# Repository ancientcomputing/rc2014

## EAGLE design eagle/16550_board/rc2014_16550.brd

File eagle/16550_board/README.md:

The board has been tested and a BIOS and associated Monitor/Debugger/BASIC binaries released.
<p>
The board is also available from OSH Park at the following link:
<p>
<a href="https://www.oshpark.com/shared_projects/1SkkN4ey"></img></a>
<p>
Note that I do not have any relationship with OSH Park other than that of a customer.
<p>
Copyright Ben Chong and licensed freely back to the community.

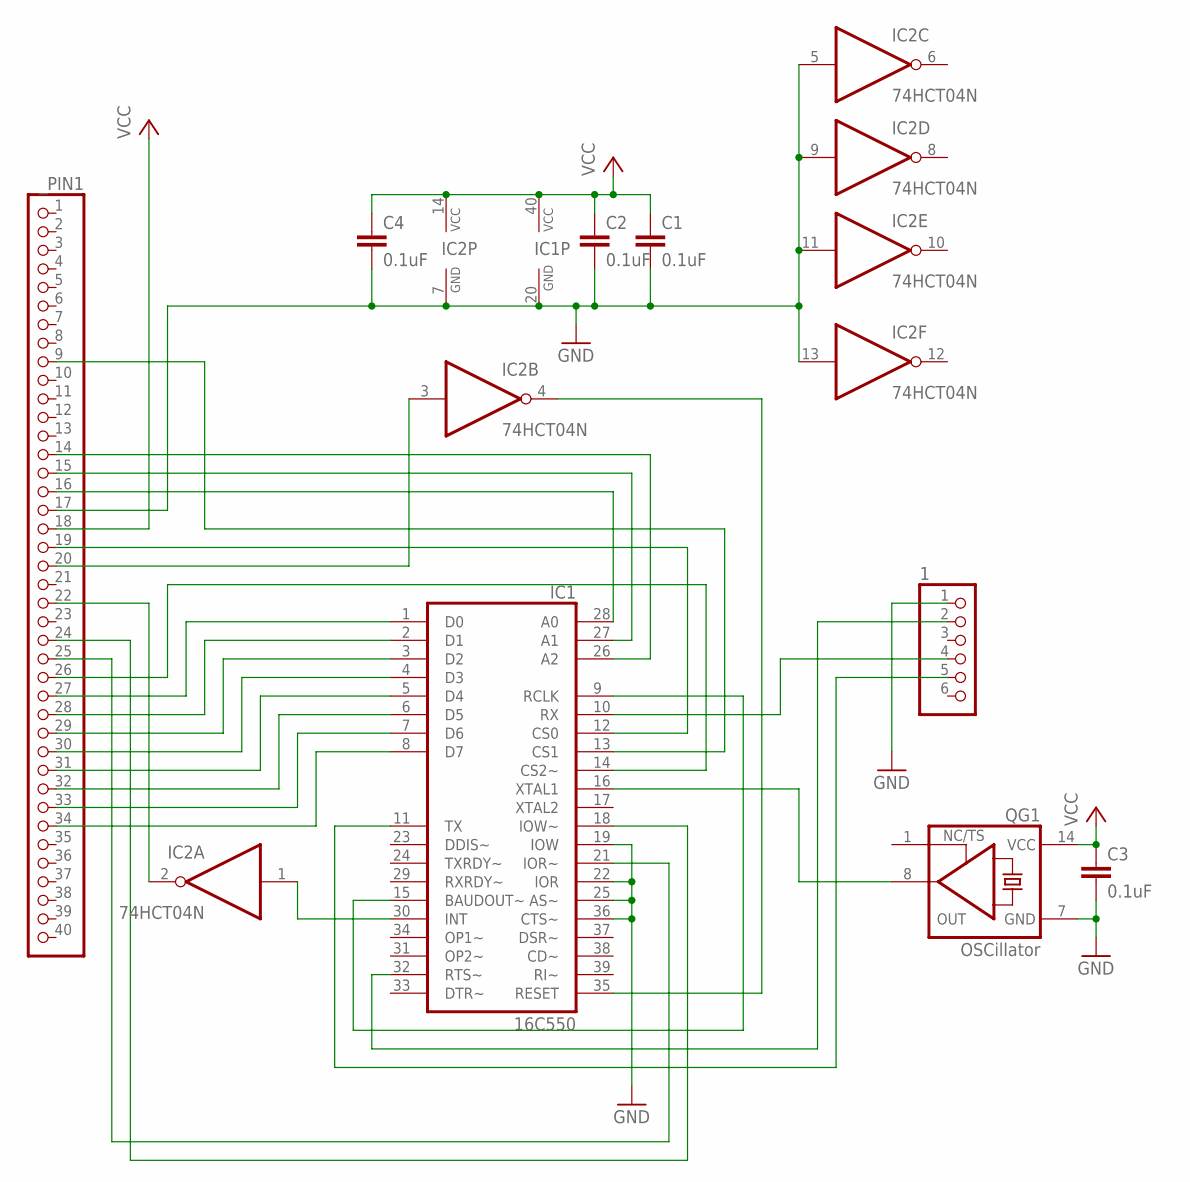
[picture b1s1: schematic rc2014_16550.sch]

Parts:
1: PINHD-1X6; 1X06
C1, C2, C3, C4: 0.1uF; C050-024X044
IC1: 16C550; DIL40
IC2: 74HCT04N; DIL14
QG1: OSCillator; DIL14S
_PIN1: PINHD-1X40; 1X40

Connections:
/INT: IC2.2 (O), _PIN1.22
/IORQ: IC1.14 (CS2~), _PIN1.26
/M1: IC1.12 (CS0), _PIN1.19
/RD: IC1.21 (IOR~), _PIN1.25
/RST: IC2.3 (I), _PIN1.20
/RTS: 1.2, IC1.32 (RTS~)
/WR: IC1.18 (IOW~), _PIN1.24
A0: IC1.28 (A0), _PIN1.16
A1: IC1.27 (A1), _PIN1.15
A2: IC1.26 (A2), _PIN1.14
A7: IC1.13 (CS1), _PIN1.9
D0: IC1.1 (D0), _PIN1.27
D1: IC1.2 (D1), _PIN1.28
D2: IC1.3 (D2), _PIN1.29
D3: IC1.4 (D3), _PIN1.30
D4: IC1.5 (D4), _PIN1.31
D5: IC1.6 (D5), _PIN1.32
D6: IC1.7 (D6), _PIN1.33
D7: IC1.8 (D7), _PIN1.34
GND: 1.1, C1.2, C2.2, C3.2, C4.2, IC1.19 (IOW), IC1.20 (GND), IC1.22 (IOR), IC1.25 (AS~), IC1.36 (CTS~), IC2.5 (I), IC2.7 (GND), IC2.9 (I), IC2.11 (I), IC2.13 (I), QG1.7 (GND), _PIN1.17
INT: IC1.30 (INT), IC2.1 (I)
unnamed: IC1.9 (RCLK), IC1.15 (BAUDOUT~)
OSC: IC1.16 (XTAL1), QG1.8 (OUT)
RESET: IC1.35 (RESET), IC2.4 (O)
RX: 1.4, IC1.10 (RX)
TX: 1.5, IC1.11 (TX)
VCC: C1.1, C2.1, C3.1, C4.1, IC1.40 (VCC), IC2.14 (VCC), QG1.14 (VCC), _PIN1.18

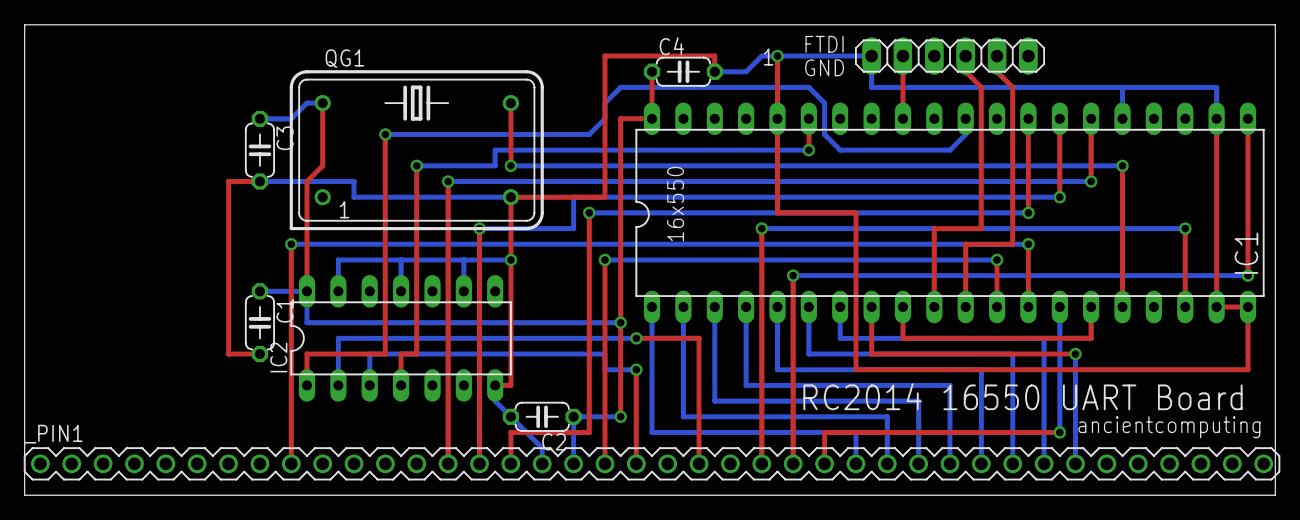
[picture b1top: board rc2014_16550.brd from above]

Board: 2 copper layers, 101.3 x 38.1 mm, 9 parts (0 on the bottom side), 27 nets.

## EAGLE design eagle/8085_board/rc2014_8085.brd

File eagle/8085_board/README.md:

<b>8085 Processor Board for the RC2014</b>
<p>
Exposes SID/SOD to an FTDI header for UART-less serial.
<p>
Tested. Wiring error between reset RC network and pin 13 of he 74xx14. Fixed in this version.
<p>
<a href="https://www.oshpark.com/shared_projects/jnleN9Nv"></img></a>
<p>
A simple Monitor can be found in the <a href="https://github.com/ancientcomputing/rc2014/tree/master/rom/8085">rom/8085 folder</a>.
<p>
Copyright Ben Chong and licensed freely back to the community.

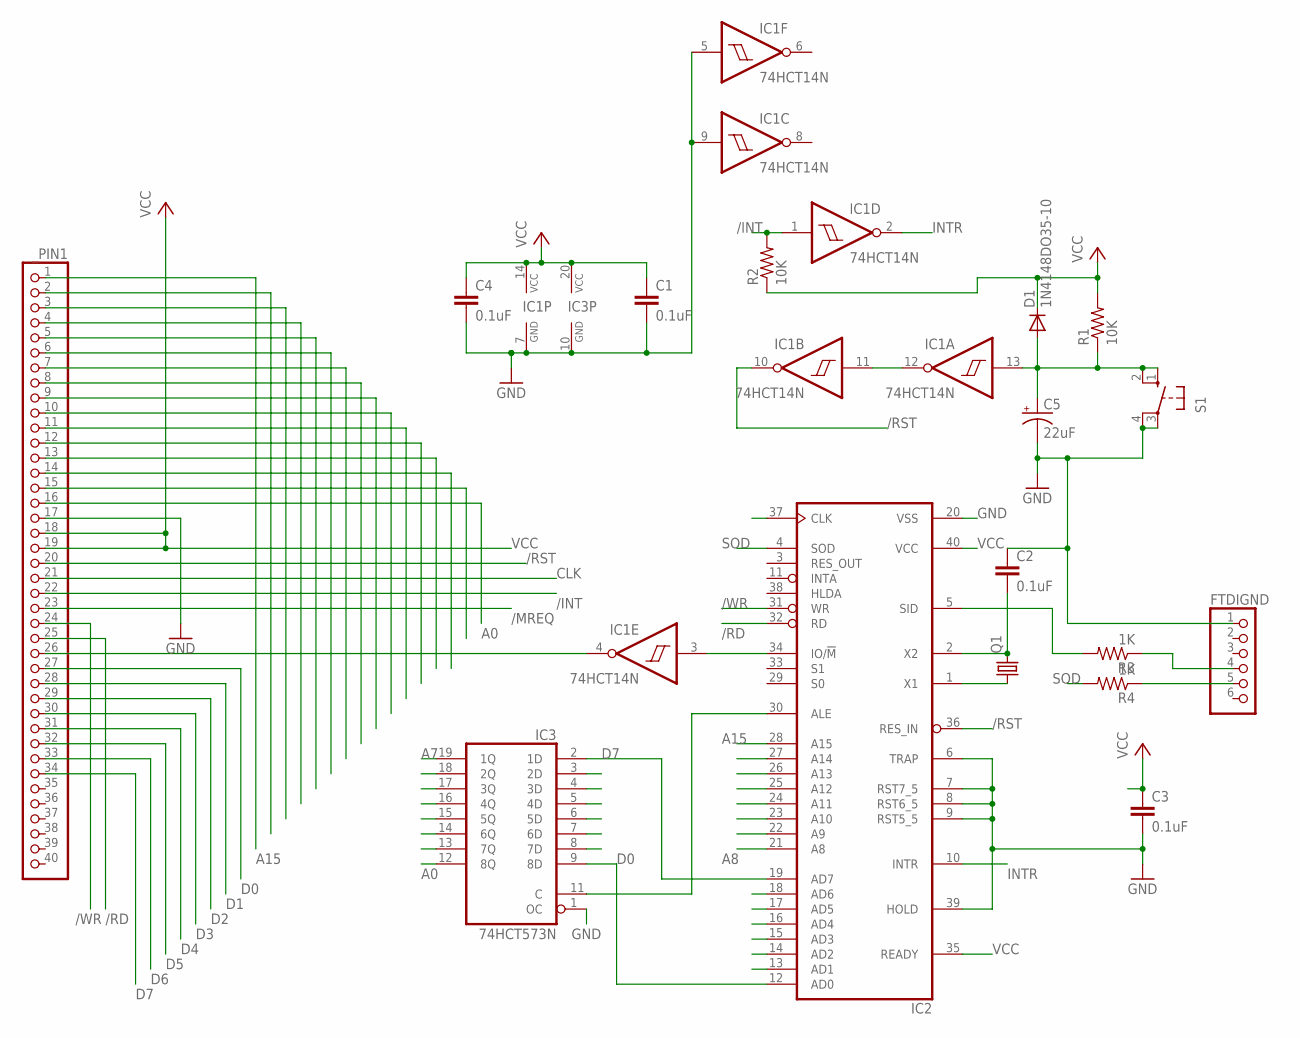
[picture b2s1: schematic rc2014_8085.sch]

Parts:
C1, C2, C3, C4: 0.1uF; C050-024X044
C5: 22uF; TAP5-80
D1: 1N4148DO35-10; DO35-10
FTDIGND: PINHD-1X6; 1X06
IC1: 74HCT14N; DIL14
IC2: 8085; DIL40
IC3: 74HCT573N; DIL20
Q1: CRYSTALHC49S; HC49/S
R1, R2: 10K; 0207/10
R3, R4: 1K; 0207/10
S1: 10-XX; B3F-10XX
_PIN1: PINHD-1X40; 1X40

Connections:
/INT: IC1.1 (I), R2.2, _PIN1.22
/IORQ: IC1.4 (O), _PIN1.26
/MREQ: IC1.3 (I), IC2.34 (IO/!M), _PIN1.23
/RD: IC2.32 (RD), _PIN1.25
/RST: IC1.10 (O), IC2.36 (RES_IN), _PIN1.20
/WR: IC2.31 (WR), _PIN1.24
A0: IC3.12 (8Q), _PIN1.16
A1: IC3.13 (7Q), _PIN1.15
A2: IC3.14 (6Q), _PIN1.14
A3: IC3.15 (5Q), _PIN1.13
A4: IC3.16 (4Q), _PIN1.12
A5: IC3.17 (3Q), _PIN1.11
A6: IC3.18 (2Q), _PIN1.10
A7: IC3.19 (1Q), _PIN1.9
A8: IC2.21 (A8), _PIN1.8
A9: IC2.22 (A9), _PIN1.7
A10: IC2.23 (A10), _PIN1.6
A11: IC2.24 (A11), _PIN1.5
A12: IC2.25 (A12), _PIN1.4
A13: IC2.26 (A13), _PIN1.3
A14: IC2.27 (A14), _PIN1.2
A15: IC2.28 (A15), _PIN1.1
ALE: IC2.30 (ALE), IC3.11 (C)
CLK: IC2.37 (CLK), _PIN1.21
D0: IC2.12 (AD0), IC3.9 (8D), _PIN1.27
D1: IC2.13 (AD1), IC3.8 (7D), _PIN1.28
D2: IC2.14 (AD2), IC3.7 (6D), _PIN1.29
D3: IC2.15 (AD3), IC3.6 (5D), _PIN1.30
D4: IC2.16 (AD4), IC3.5 (4D), _PIN1.31
D5: IC2.17 (AD5), IC3.4 (3D), _PIN1.32
D6: IC2.18 (AD6), IC3.3 (2D), _PIN1.33
D7: IC2.19 (AD7), IC3.2 (1D), _PIN1.34
GND: C1.2, C2.1, C3.2, C4.2, C5.-, FTDIGND.1, IC1.5 (I), IC1.7 (GND), IC1.9 (I), IC2.6 (TRAP), IC2.7 (RST7_5), IC2.8 (RST6_5), IC2.9 (RST5_5), IC2.20 (VSS), IC2.39 (HOLD), IC3.1 (OC), IC3.10 (GND), S1.3, S1.4 (P1), _PIN1.17
INTR: IC1.2 (O), IC2.10 (INTR)
unnamed: IC2.1 (X1), Q1.1
unnamed: C2.2, IC2.2 (X2), Q1.2
unnamed: IC1.11 (I), IC1.12 (O)
RESET: C5.+, D1.A, IC1.13 (I), R1.1, S1.1 (S), S1.2 (S1)
RX: FTDIGND.4, R3.1
SID: IC2.5 (SID), R3.2
SOD: IC2.4 (SOD), R4.2
TX: FTDIGND.5, R4.1
VCC: C1.1, C3.1, C4.1, D1.C, IC1.14 (VCC), IC2.35 (READY), IC2.40 (VCC), IC3.20 (VCC), R1.2, R2.1, _PIN1.18, _PIN1.19

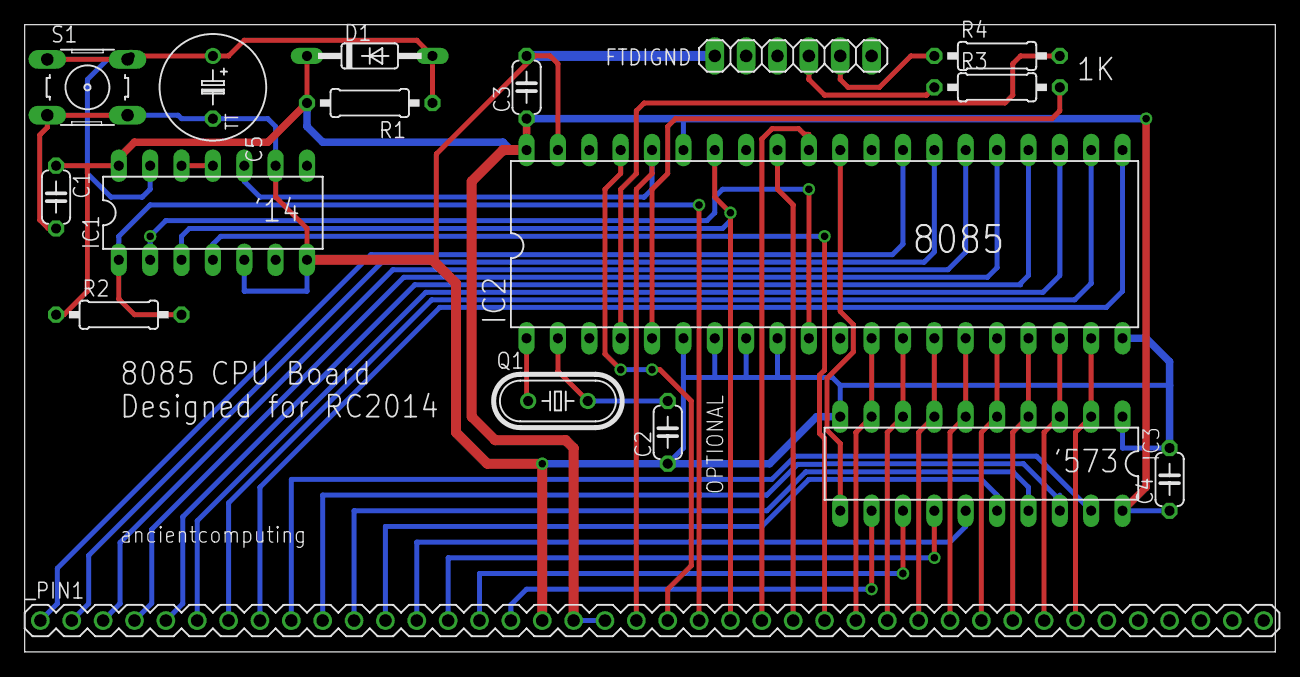
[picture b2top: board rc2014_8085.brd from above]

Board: 2 copper layers, 101.3 x 50.8 mm, 17 parts (0 on the bottom side), 43 nets.

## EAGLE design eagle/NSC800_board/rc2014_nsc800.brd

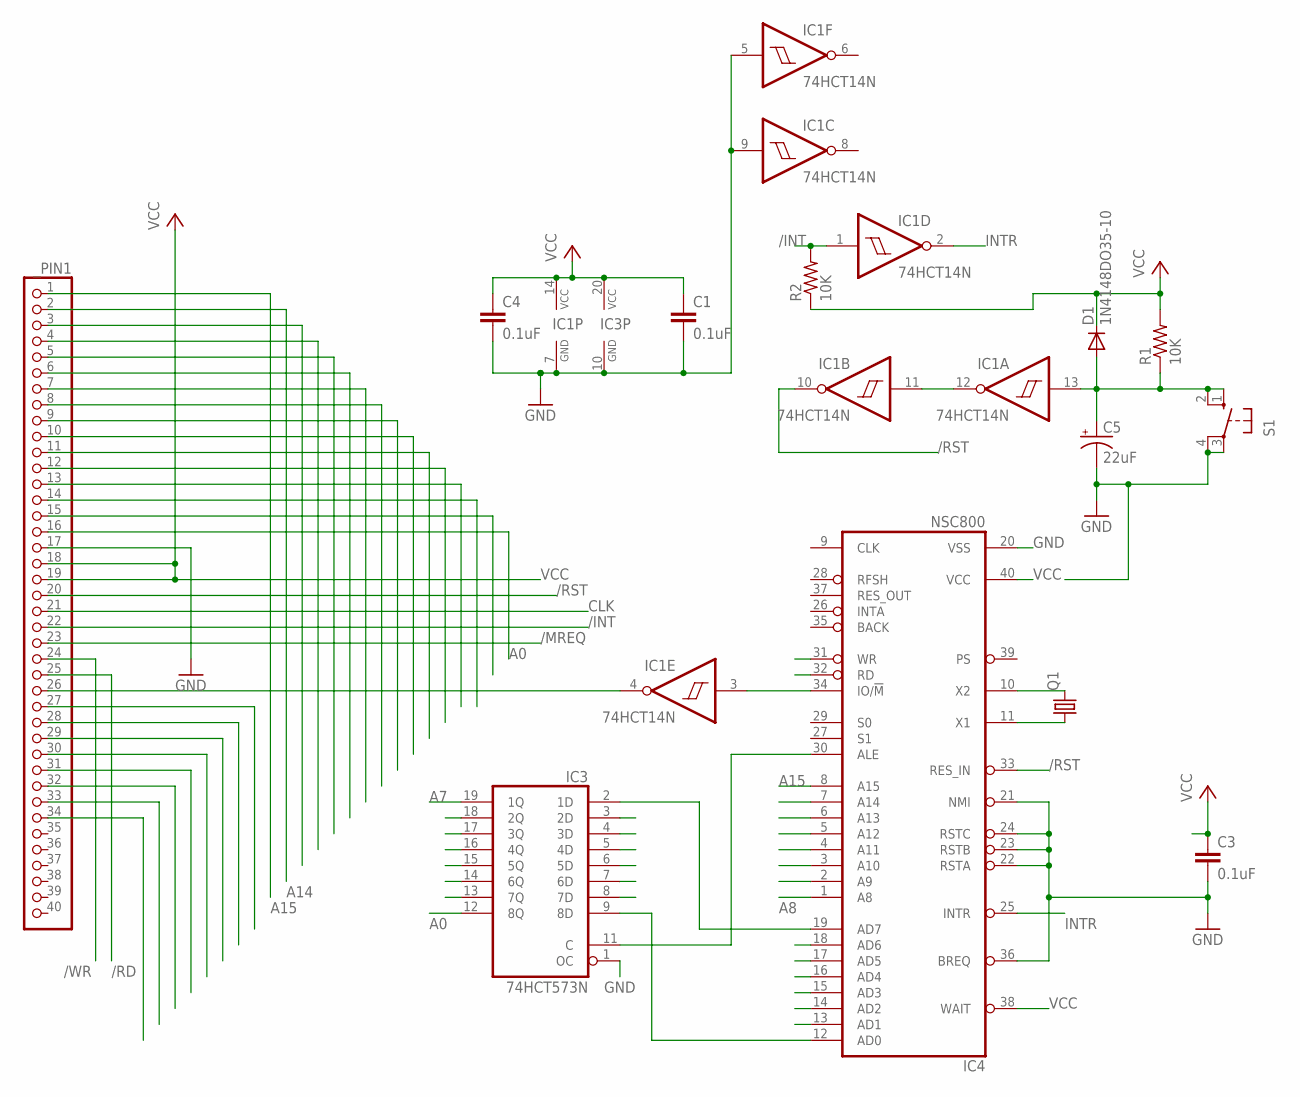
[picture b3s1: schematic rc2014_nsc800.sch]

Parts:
C1, C3, C4: 0.1uF; C050-024X044
C5: 22uF; TAP5-80
D1: 1N4148DO35-10; DO35-10
IC1: 74HCT14N; DIL14
IC3: 74HCT573N; DIL20
IC4: NSC800; DIL40
Q1: CRYSTALHC49S; HC49/S
R1, R2: 10K; 0207/10
S1: 10-XX; B3F-10XX
_PIN1: PINHD-1X40; 1X40

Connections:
/INT: IC1.1 (I), R2.2, _PIN1.22
/IORQ: IC1.4 (O), _PIN1.26
/MREQ: IC1.3 (I), IC4.34 (IO/!M), _PIN1.23
/RD: IC4.32 (RD), _PIN1.25
/RST: IC1.10 (O), IC4.33 (RES_IN), _PIN1.20
/WR: IC4.31 (WR), _PIN1.24
A0: IC3.12 (8Q), _PIN1.16
A1: IC3.13 (7Q), _PIN1.15
A2: IC3.14 (6Q), _PIN1.14
A3: IC3.15 (5Q), _PIN1.13
A4: IC3.16 (4Q), _PIN1.12
A5: IC3.17 (3Q), _PIN1.11
A6: IC3.18 (2Q), _PIN1.10
A7: IC3.19 (1Q), _PIN1.9
A8: IC4.1 (A8), _PIN1.8
A9: IC4.2 (A9), _PIN1.7
A10: IC4.3 (A10), _PIN1.6
A11: IC4.4 (A11), _PIN1.5
A12: IC4.5 (A12), _PIN1.4
A13: IC4.6 (A13), _PIN1.3
A14: IC4.7 (A14), _PIN1.2
A15: IC4.8 (A15), _PIN1.1
CLK: _PIN1.21
D0: IC3.9 (8D), IC4.12 (AD0), _PIN1.27
D1: IC3.8 (7D), IC4.13 (AD1), _PIN1.28
D2: IC3.7 (6D), IC4.14 (AD2), _PIN1.29
D3: IC3.6 (5D), IC4.15 (AD3), _PIN1.30
D4: IC3.5 (4D), IC4.16 (AD4), _PIN1.31
D5: IC3.4 (3D), IC4.17 (AD5), _PIN1.32
D6: IC3.3 (2D), IC4.18 (AD6), _PIN1.33
D7: IC3.2 (1D), IC4.19 (AD7), _PIN1.34
GND: C1.2, C3.2, C4.2, C5.-, IC1.5 (I), IC1.7 (GND), IC1.9 (I), IC3.1 (OC), IC3.10 (GND), IC4.20 (VSS), IC4.21 (NMI), IC4.22 (RSTA), IC4.23 (RSTB), IC4.24 (RSTC), IC4.36 (BREQ), S1.3, S1.4 (P1), _PIN1.17
INTR: IC1.2 (O), IC4.25 (INTR)
unnamed: IC3.11 (C), IC4.30 (ALE)
unnamed: IC4.11 (X1), Q1.1
unnamed: IC4.10 (X2), Q1.2
unnamed: IC1.11 (I), IC1.12 (O)
RESET: C5.+, D1.A, IC1.13 (I), R1.1, S1.1 (S), S1.2 (S1)
VCC: C1.1, C3.1, C4.1, D1.C, IC1.14 (VCC), IC3.20 (VCC), IC4.38 (WAIT), IC4.40 (VCC), R1.2, R2.1, _PIN1.18, _PIN1.19

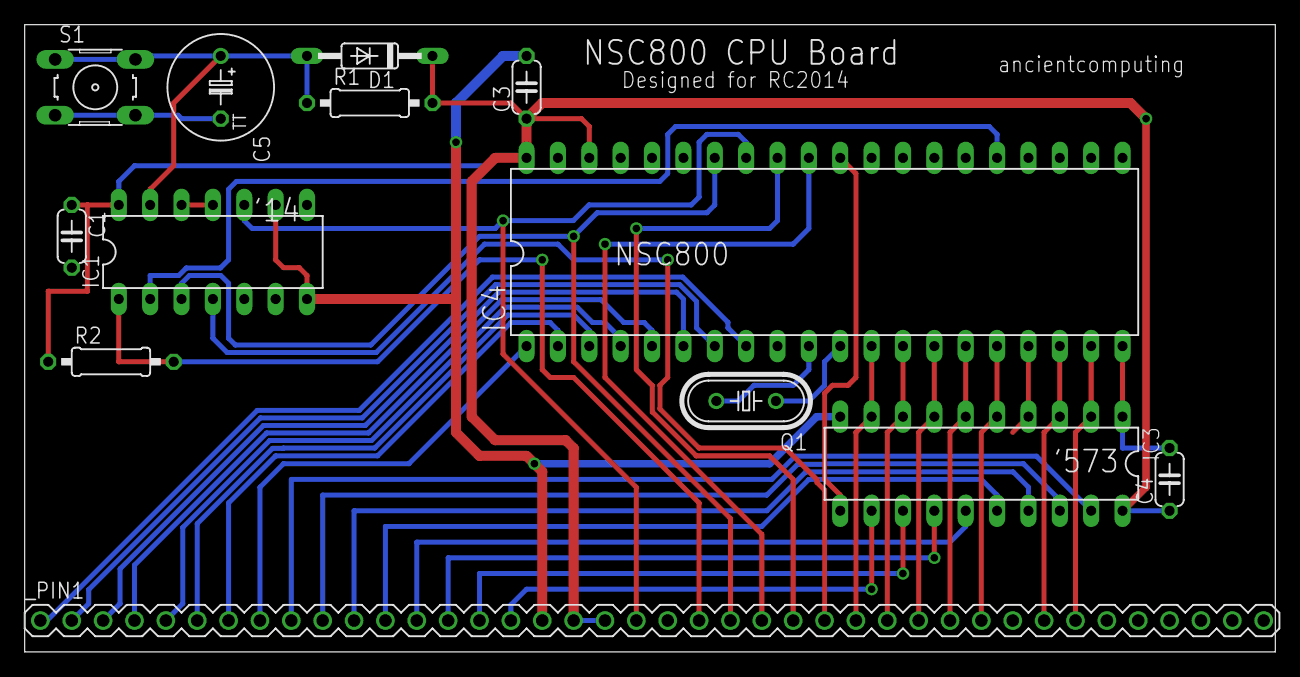
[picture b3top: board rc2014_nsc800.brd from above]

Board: 2 copper layers, 101.3 x 50.8 mm, 13 parts (0 on the bottom side), 38 nets.

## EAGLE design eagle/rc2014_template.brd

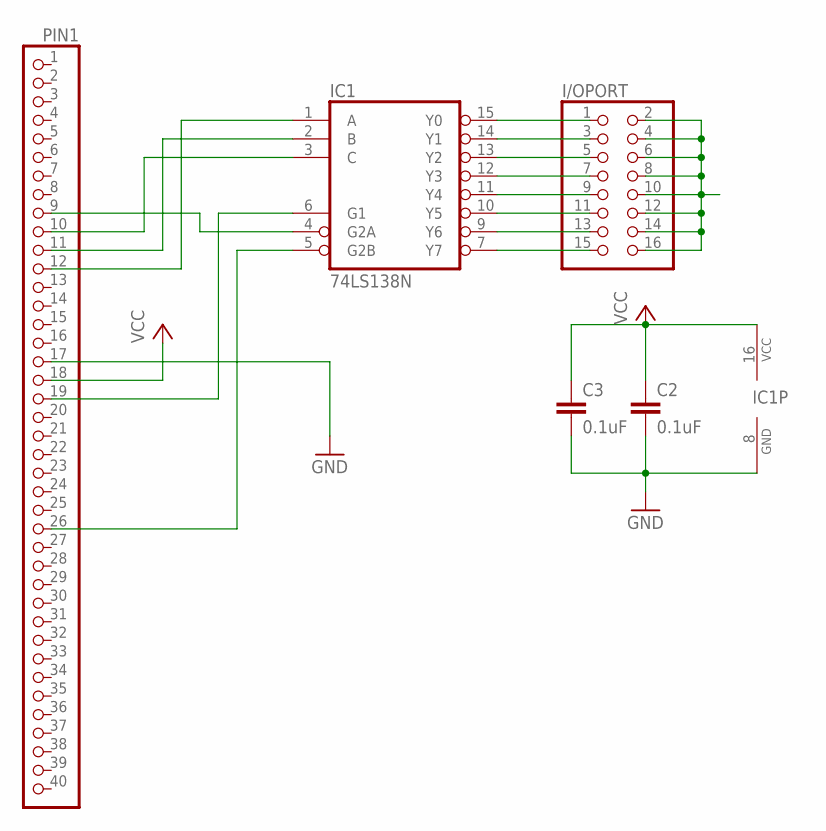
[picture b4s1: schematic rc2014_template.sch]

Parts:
C2, C3: 0.1uF; C050-024X044
I/OPORT: PINHD-2X8; 2X08
IC1: 74LS138N; DIL16
PIN1: PINHD-1X40; 1X40

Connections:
GND: C2.2, C3.2, IC1.8 (GND), PIN1.17
unnamed: IC1.6 (G1), PIN1.19
unnamed: IC1.5 (G2B), PIN1.26
unnamed: IC1.4 (G2A), PIN1.9
unnamed: IC1.3 (C), PIN1.10
unnamed: IC1.2 (B), PIN1.11
unnamed: IC1.1 (A), PIN1.12
unnamed: I/OPORT.1, IC1.15 (Y0)
unnamed: I/OPORT.3, IC1.14 (Y1)
unnamed: I/OPORT.5, IC1.13 (Y2)
unnamed: I/OPORT.7, IC1.12 (Y3)
unnamed: I/OPORT.9, IC1.11 (Y4)
unnamed: I/OPORT.11, IC1.10 (Y5)
unnamed: I/OPORT.13, IC1.9 (Y6)
unnamed: I/OPORT.15, IC1.7 (Y7)
unnamed: I/OPORT.2, I/OPORT.4, I/OPORT.6, I/OPORT.8, I/OPORT.10, I/OPORT.12, I/OPORT.14, I/OPORT.16
VCC: C2.1, C3.1, IC1.16 (VCC), PIN1.18

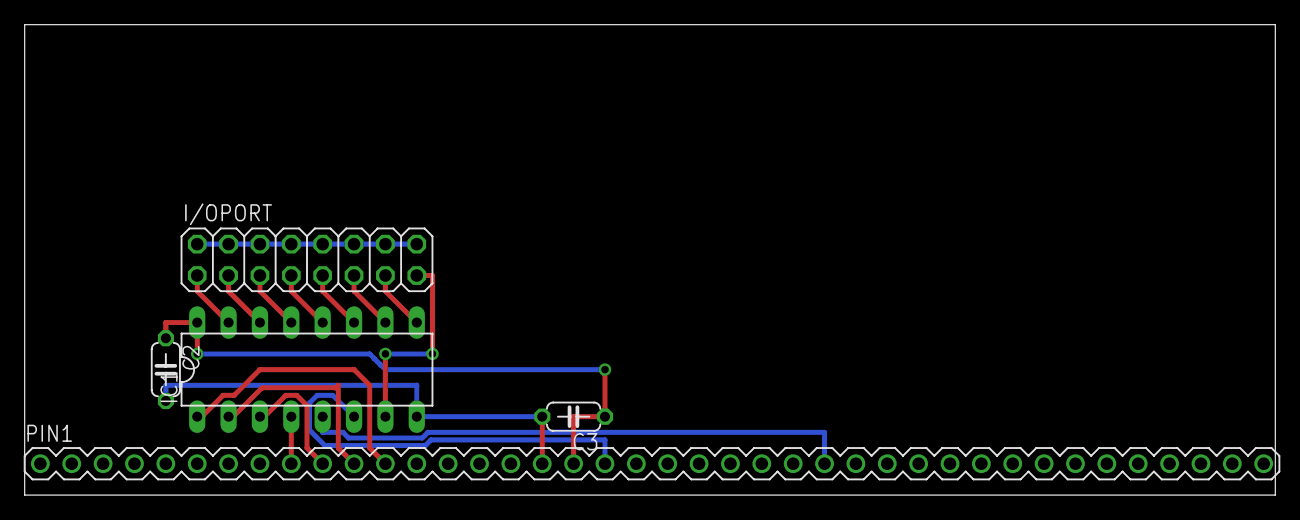
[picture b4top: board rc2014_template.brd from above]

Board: 2 copper layers, 101.3 x 38.1 mm, 5 parts (0 on the bottom side), 17 nets.

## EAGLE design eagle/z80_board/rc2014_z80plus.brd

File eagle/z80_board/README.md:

The board is available from OSH Park at the following link:
<p>
<a href="https://www.oshpark.com/shared_projects/LhvI0uAs"></img></a>
<p>
Copyright Ben Chong and freely licensed back to the community.

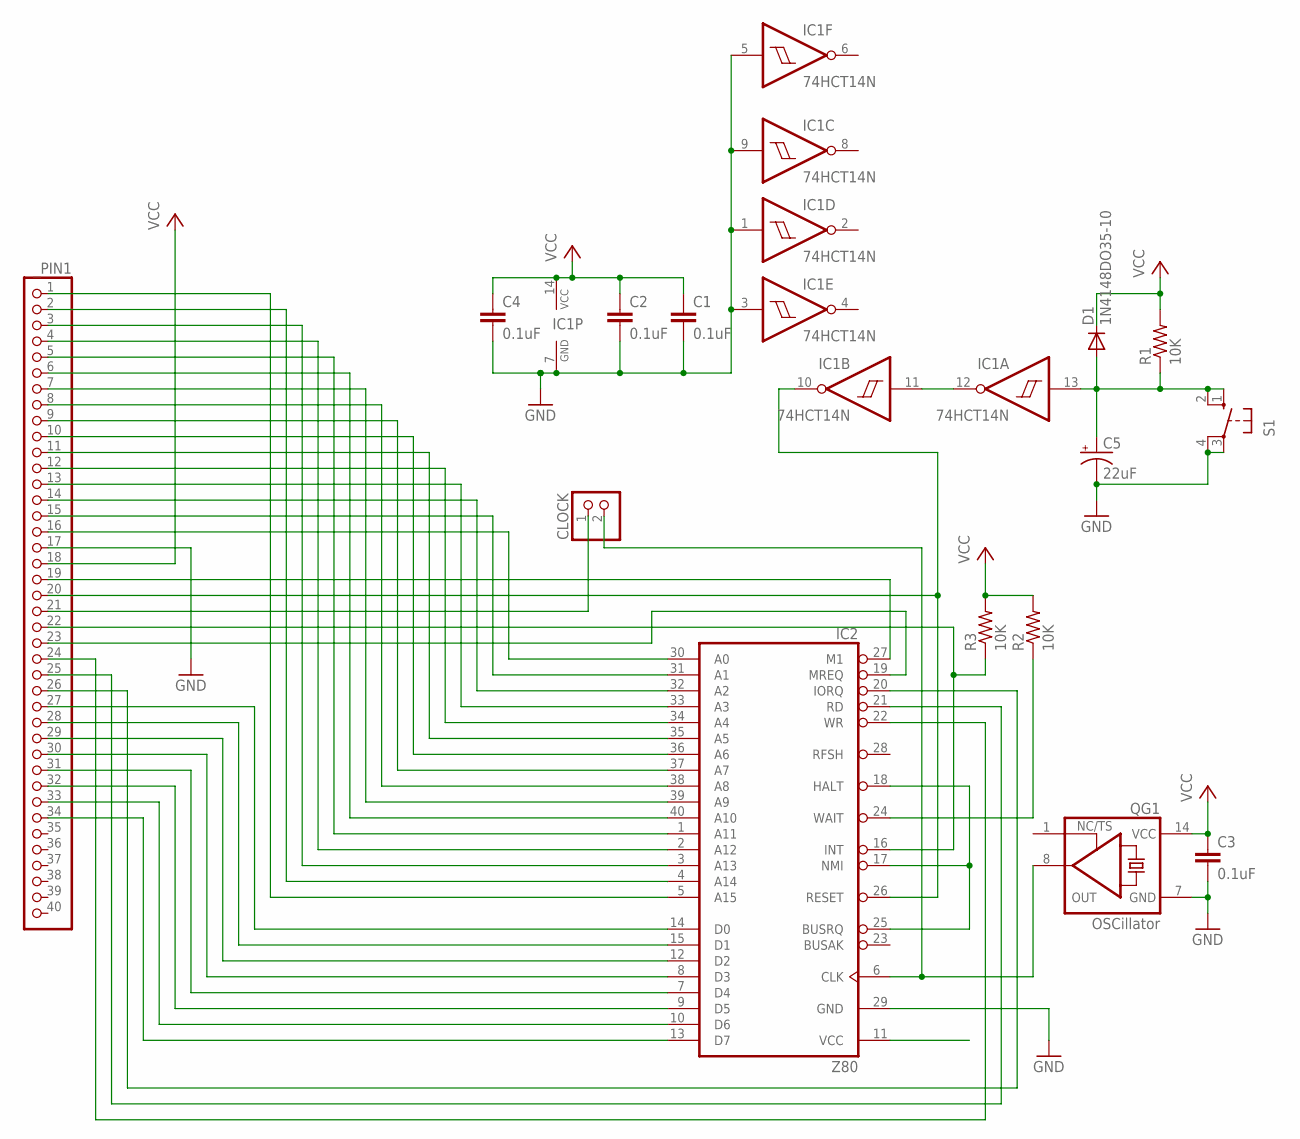
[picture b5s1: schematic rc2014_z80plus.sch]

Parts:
C1, C2, C3, C4: 0.1uF; C050-024X044
C5: 22uF; TAP5-80
CLOCK: PINHD-1X2; 1X02
D1: 1N4148DO35-10; DO35-10
IC1: 74HCT14N; DIL14
IC2: Z80; DIL40
QG1: OSCillator; DIL14S
R1, R2, R3: 10K; 0207/10
S1: 10-XX; B3F-10XX
_PIN1: PINHD-1X40; 1X40

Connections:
/INT: IC2.16 (INT), R3.1, _PIN1.22
/IORQ: IC2.20 (IORQ), _PIN1.26
/M1: IC2.27 (M1), _PIN1.19
/MREQ: IC2.19 (MREQ), _PIN1.23
/RD: IC2.21 (RD), _PIN1.25
/RST: IC1.10 (O), IC2.26 (RESET), _PIN1.20
/WAIT: IC2.24 (WAIT), R2.1
/WR: IC2.22 (WR), _PIN1.24
A0: IC2.30 (A0), _PIN1.16
A1: IC2.31 (A1), _PIN1.15
A2: IC2.32 (A2), _PIN1.14
A3: IC2.33 (A3), _PIN1.13
A4: IC2.34 (A4), _PIN1.12
A5: IC2.35 (A5), _PIN1.11
A6: IC2.36 (A6), _PIN1.10
A7: IC2.37 (A7), _PIN1.9
A8: IC2.38 (A8), _PIN1.8
A9: IC2.39 (A9), _PIN1.7
A10: IC2.40 (A10), _PIN1.6
A11: IC2.1 (A11), _PIN1.5
A12: IC2.2 (A12), _PIN1.4
A13: IC2.3 (A13), _PIN1.3
A14: IC2.4 (A14), _PIN1.2
A15: IC2.5 (A15), _PIN1.1
CLK: CLOCK.1, _PIN1.21
D0: IC2.14 (D0), _PIN1.27
D1: IC2.15 (D1), _PIN1.28
D2: IC2.12 (D2), _PIN1.29
D3: IC2.8 (D3), _PIN1.30
D4: IC2.7 (D4), _PIN1.31
D5: IC2.9 (D5), _PIN1.32
D6: IC2.10 (D6), _PIN1.33
D7: IC2.13 (D7), _PIN1.34
GND: C1.2, C2.2, C3.2, C4.2, C5.-, IC1.1 (I), IC1.3 (I), IC1.5 (I), IC1.7 (GND), IC1.9 (I), IC2.29 (GND), QG1.7 (GND), S1.3, S1.4 (P1), _PIN1.17
unnamed: IC1.11 (I), IC1.12 (O)
OSC: CLOCK.2, IC2.6 (CLK), QG1.8 (OUT)
RESET: C5.+, D1.A, IC1.13 (I), R1.1, S1.1 (S), S1.2 (S1)
VCC: C1.1, C2.1, C3.1, C4.1, D1.C, IC1.14 (VCC), IC2.11 (VCC), IC2.17 (NMI), IC2.18 (HALT), IC2.25 (BUSRQ), QG1.14 (VCC), R1.2, R2.2, R3.2, _PIN1.18

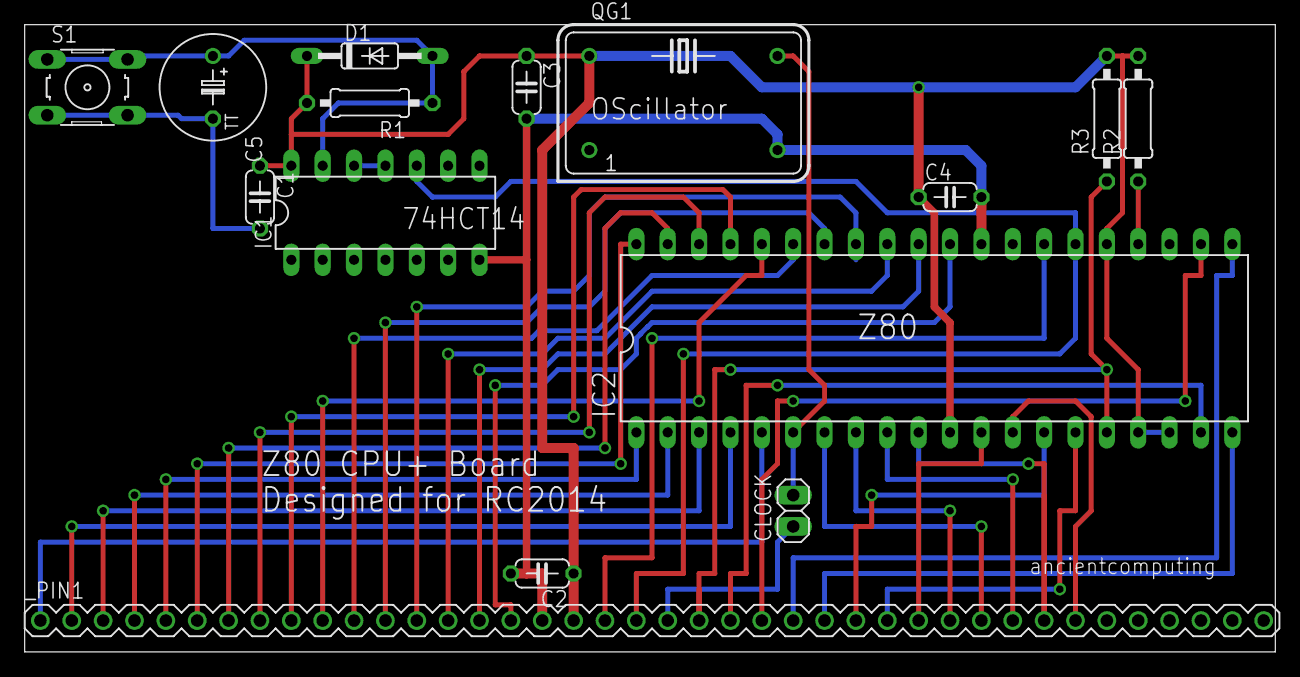
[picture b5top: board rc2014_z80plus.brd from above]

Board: 2 copper layers, 101.3 x 50.8 mm, 15 parts (0 on the bottom side), 38 nets.
